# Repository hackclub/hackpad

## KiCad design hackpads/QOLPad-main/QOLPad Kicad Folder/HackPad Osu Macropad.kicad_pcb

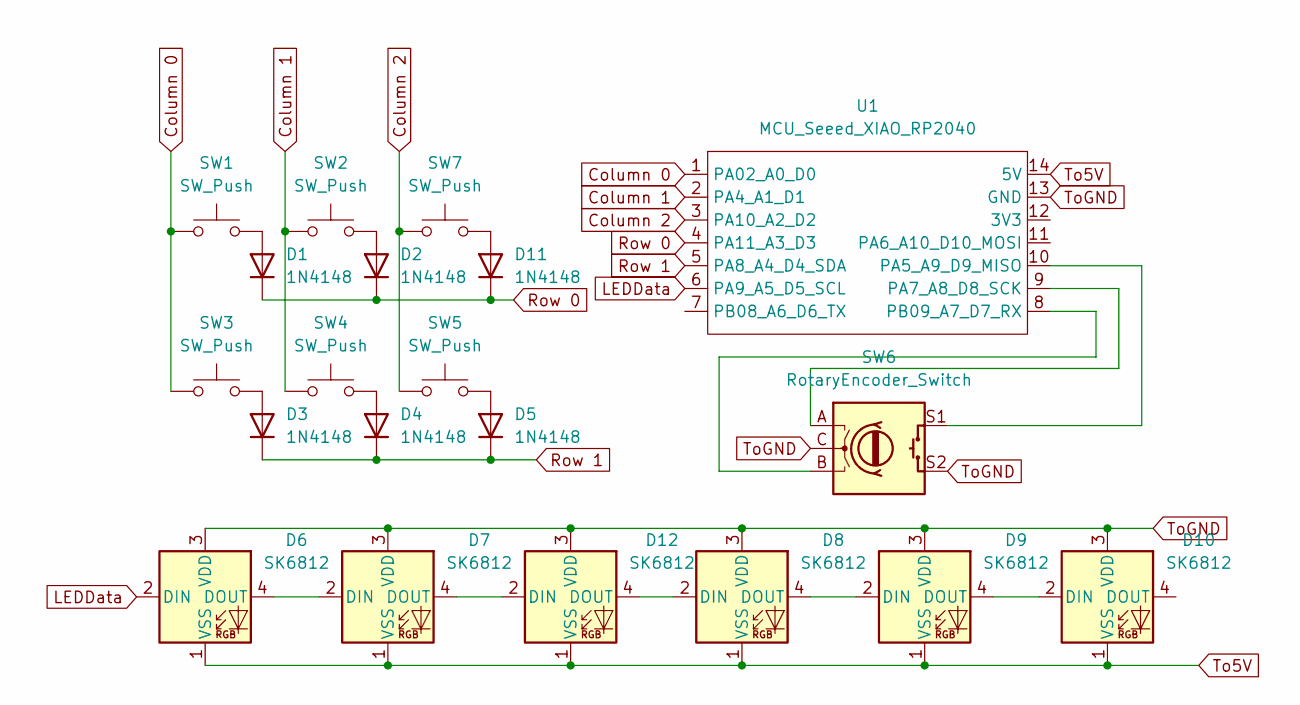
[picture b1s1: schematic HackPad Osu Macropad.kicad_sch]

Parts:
D1, D2, D3, D4, D5, D11: 1N4148; D_DO-35_SOD27_P7.62mm_Horizontal
D6, D7, D8, D9, D10, D12: SK6812; SK6812MINI-E
SW1, SW2, SW3, SW4, SW5, SW7: SW_Push; SW_Cherry_MX_1.00u_PCB
SW6: RotaryEncoder_Switch; RotaryEncoder_Alps_EC11E-Switch_Vertical_H20mm_CircularMoun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
U1: MCU_Seeed_XIAO_RP2040; XIAO-RP2040

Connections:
Column 0: SW1.1, SW3.1, U1.1 (PA02_A0_D0)
Column 1: SW2.1, SW4.1, U1.2 (PA4_A1_D1)
Column 2: SW5.1, SW7.1, U1.3 (PA10_A2_D2)
LEDData: D6.2 (DIN), U1.6 (PA9_A5_D5_SCL)
unnamed: D1.2 (A), SW1.2
unnamed: D2.2 (A), SW2.2
unnamed: D3.2 (A), SW3.2
unnamed: D4.2 (A), SW4.2
unnamed: D5.2 (A), SW5.2
unnamed: D6.4 (DOUT), D7.2 (DIN)
unnamed: D8.4 (DOUT), D9.2 (DIN)
unnamed: D9.4 (DOUT), D10.2 (DIN)
unnamed: D11.2 (A), SW7.2
unnamed: D7.4 (DOUT), D12.2 (DIN)
unnamed: D8.2 (DIN), D12.4 (DOUT)
unnamed: SW6.S1, U1.10 (PA5_A9_D9_MISO)
unnamed: SW6.A, U1.9 (PA7_A8_D8_SCK)
unnamed: SW6.B, U1.8 (PB09_A7_D7_RX)
Row 0: D1.1 (K), D2.1 (K), D11.1 (K), U1.4 (PA11_A3_D3)
Row 1: D3.1 (K), D4.1 (K), D5.1 (K), U1.5 (PA8_A4_D4_SDA)
To5V: D6.1 (VSS), D7.1 (VSS), D8.1 (VSS), D9.1 (VSS), D10.1 (VSS), D12.1 (VSS), U1.14 (5V)
ToGND: D6.3 (VDD), D7.3 (VDD), D8.3 (VDD), D9.3 (VDD), D10.3 (VDD), D12.3 (VDD), SW6.C, SW6.S2, U1.13 (GND)

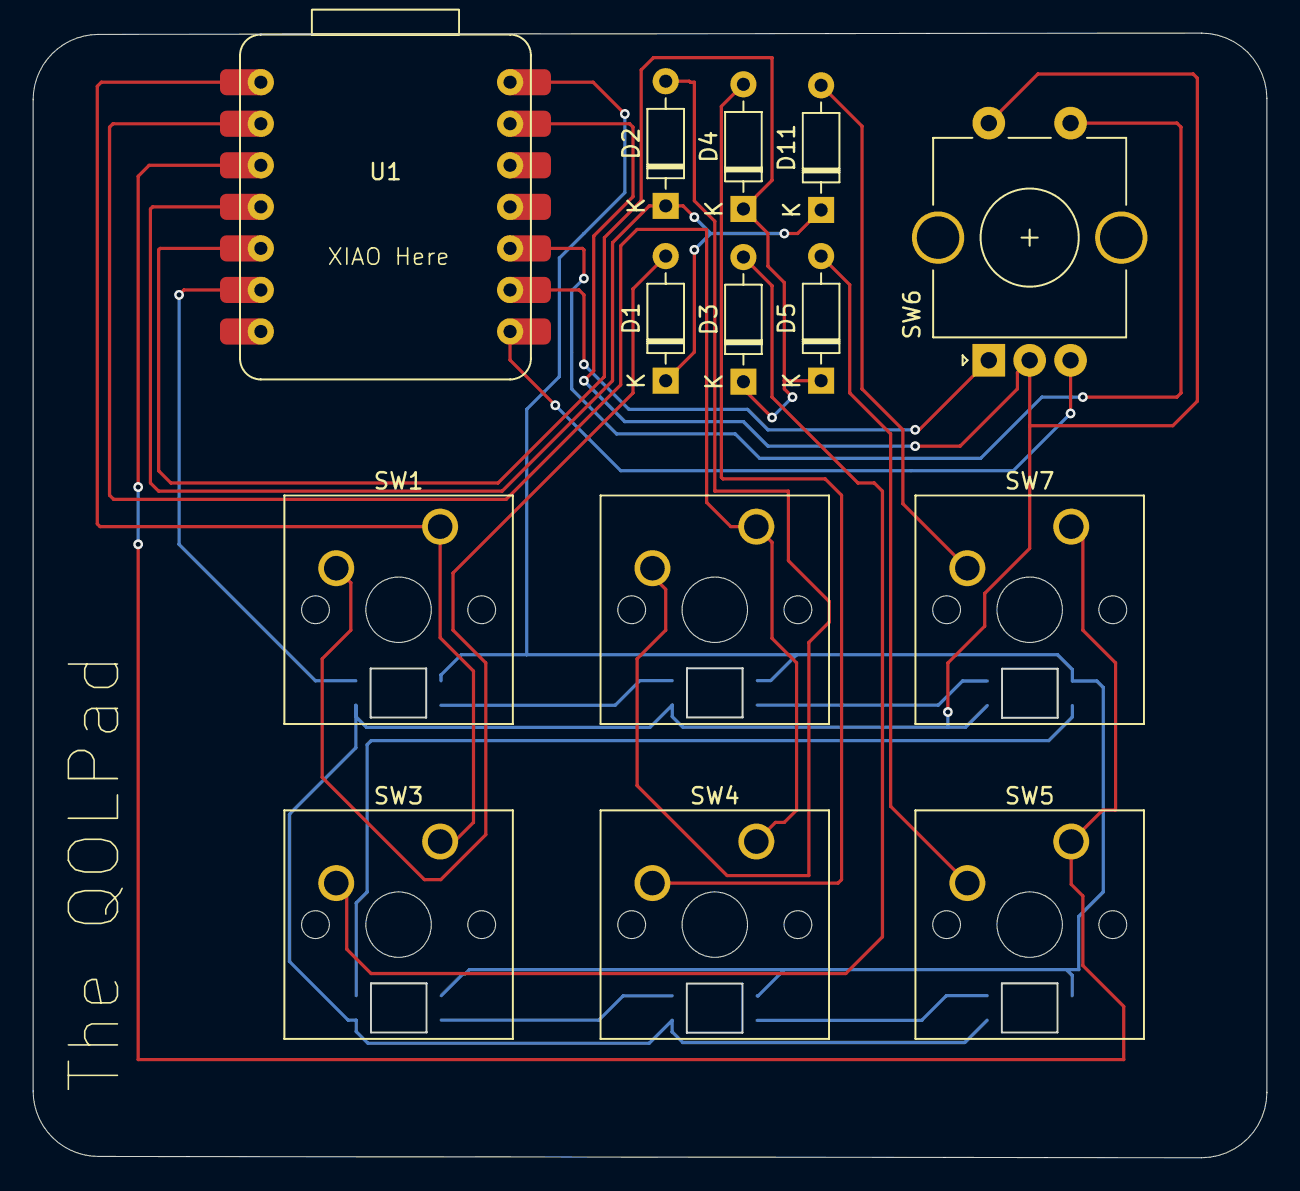
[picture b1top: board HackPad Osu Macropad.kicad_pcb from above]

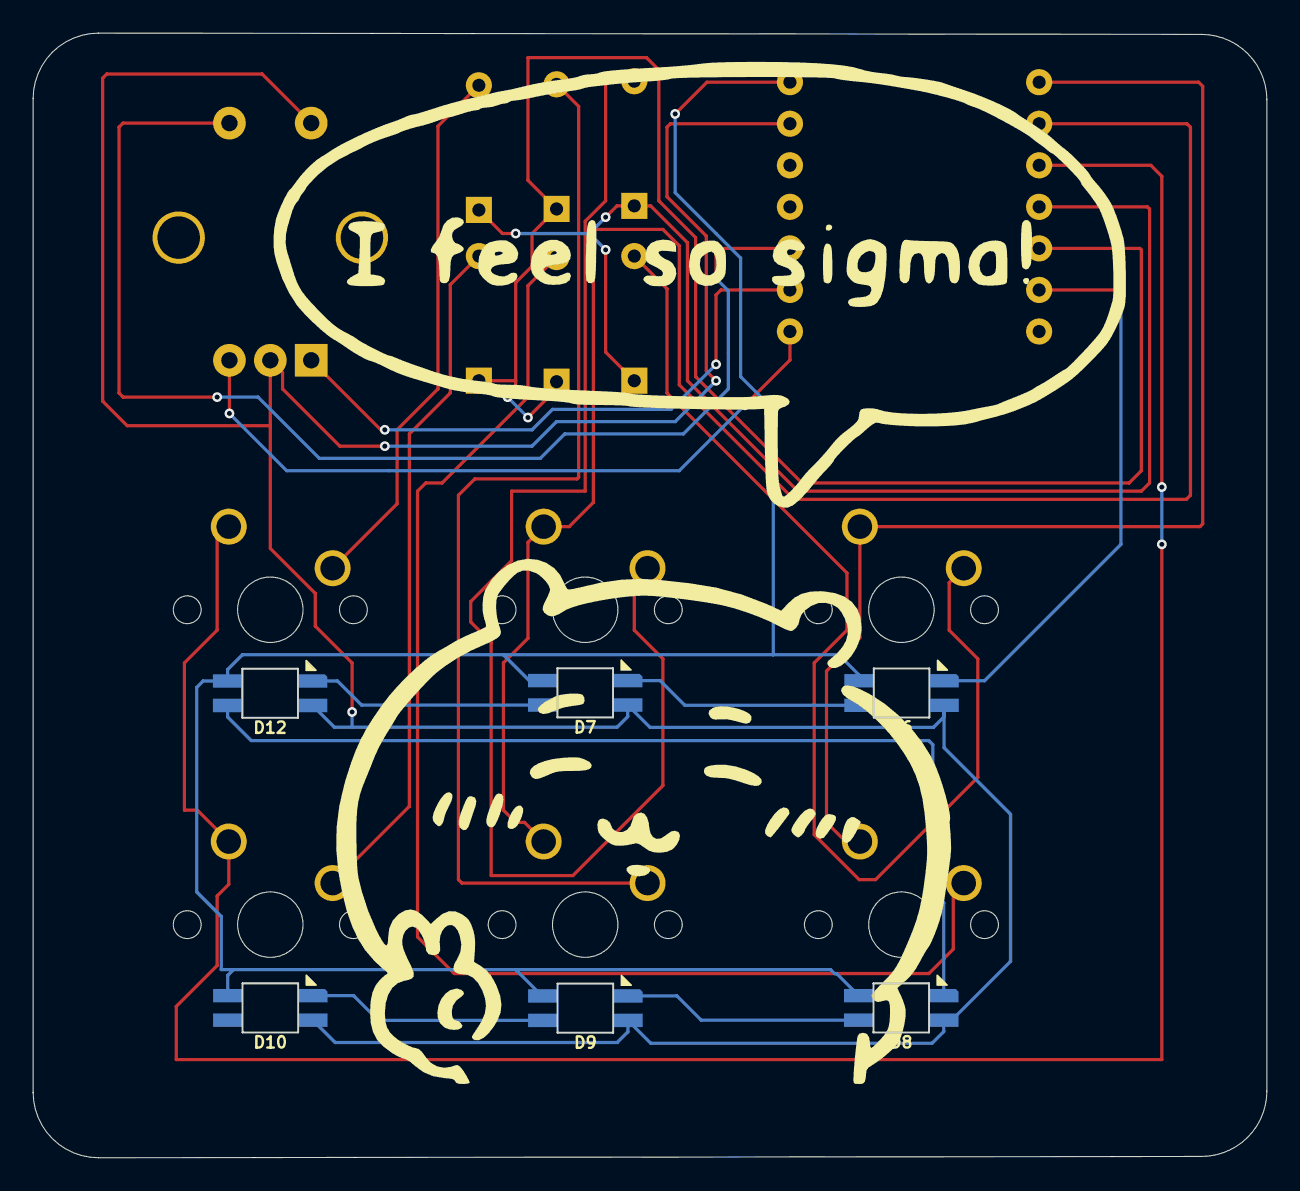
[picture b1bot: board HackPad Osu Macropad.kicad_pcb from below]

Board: 2 copper layers, 75.4 x 68.8 mm, 20 parts (6 on the bottom side), 22 nets.

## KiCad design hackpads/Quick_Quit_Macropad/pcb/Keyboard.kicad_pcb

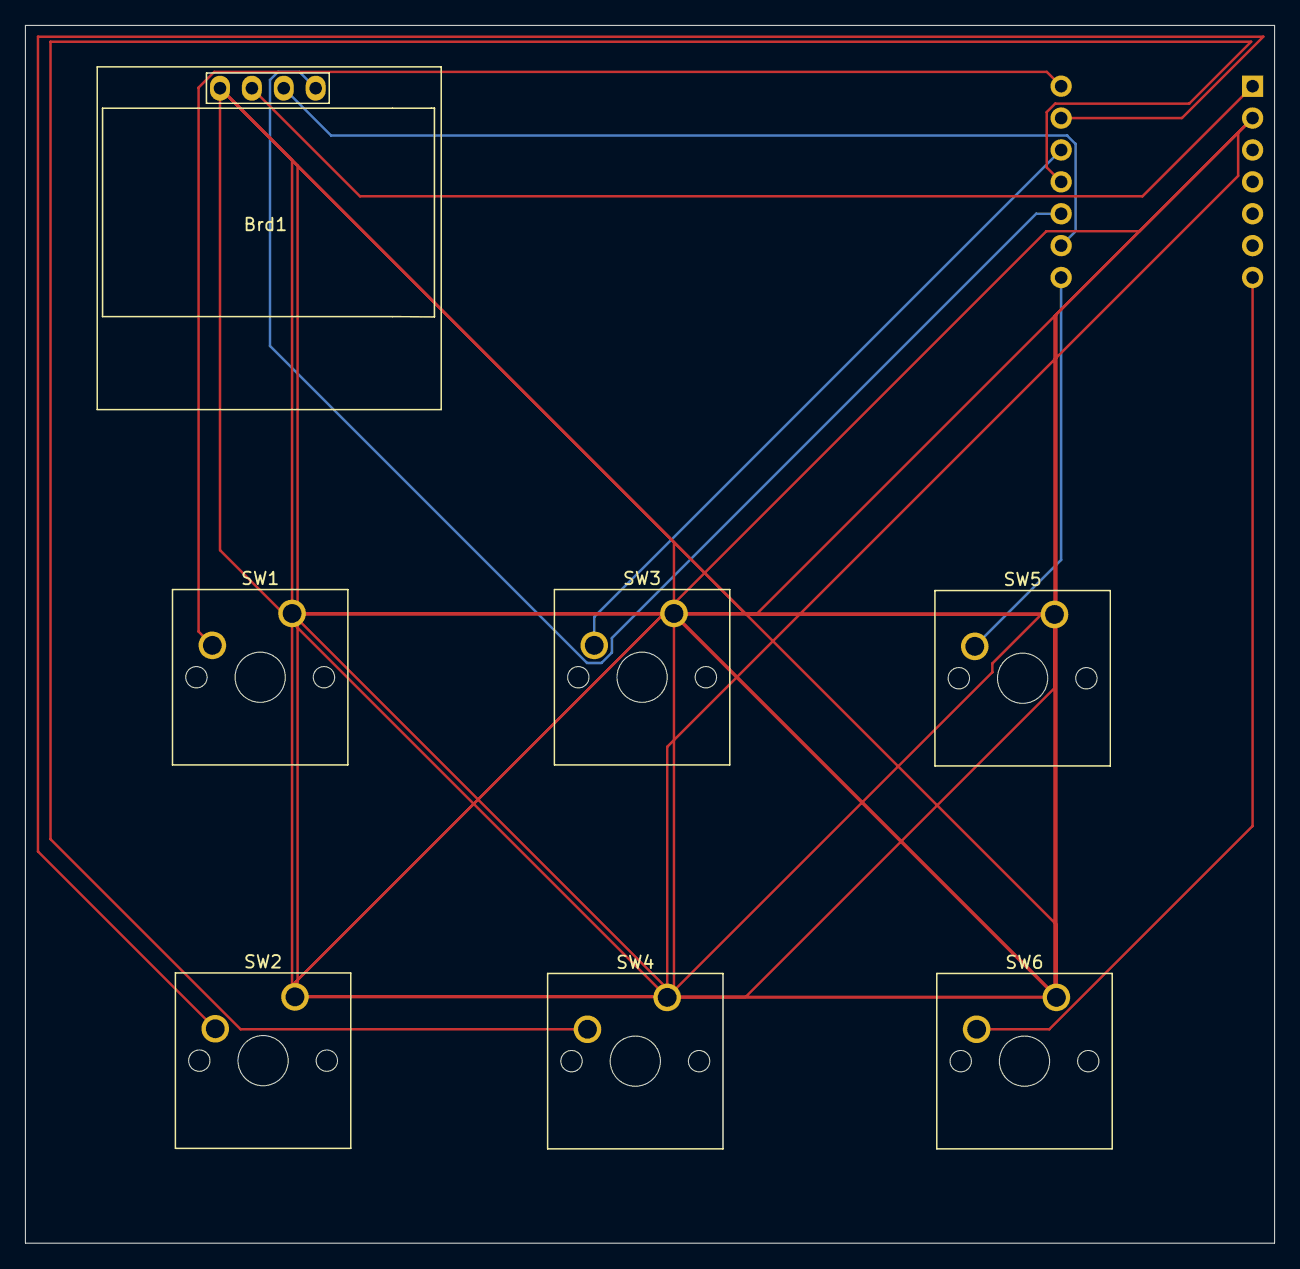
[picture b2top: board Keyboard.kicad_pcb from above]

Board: 2 copper layers, 99.5 x 97.0 mm, 8 parts (1 on the bottom side), 10 nets.

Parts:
Brd1: SSD1306; 128x64OLED
SW1, SW2, SW3, SW4, SW5, SW6: SW_Push; SW_Cherry_MX_1.00u_PCB
U1: Seeed Studio XIAO SAMD21; XIAO-Generic-Thruhole-14P-2.54-21X17.8MM

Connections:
1: SW1.2, U1.14 (5V)
2: SW2.2, U1.13 (GND)
3: SW3.2, U1.12 (3V3)
4: SW4.2, U1.11 (PA6_A10_D10_MOSI)
5: SW5.2, U1.8 (PB09_A7_D7_RX)
6: SW6.2, U1.7 (PB08_A6_D6_TX)
GND: Brd1.1 (GND), SW1.1, SW2.1, SW3.1, SW4.1, SW5.1, SW6.1, U1.2 (PA4_A1_D1)
SCL: Brd1.3 (SCL), U1.9 (PA7_A8_D8_SCK)
SDA: Brd1.4 (SDA), U1.10 (PA5_A9_D9_MISO)
VCC: Brd1.2 (VCC), U1.1 (PA02_A0_D0)

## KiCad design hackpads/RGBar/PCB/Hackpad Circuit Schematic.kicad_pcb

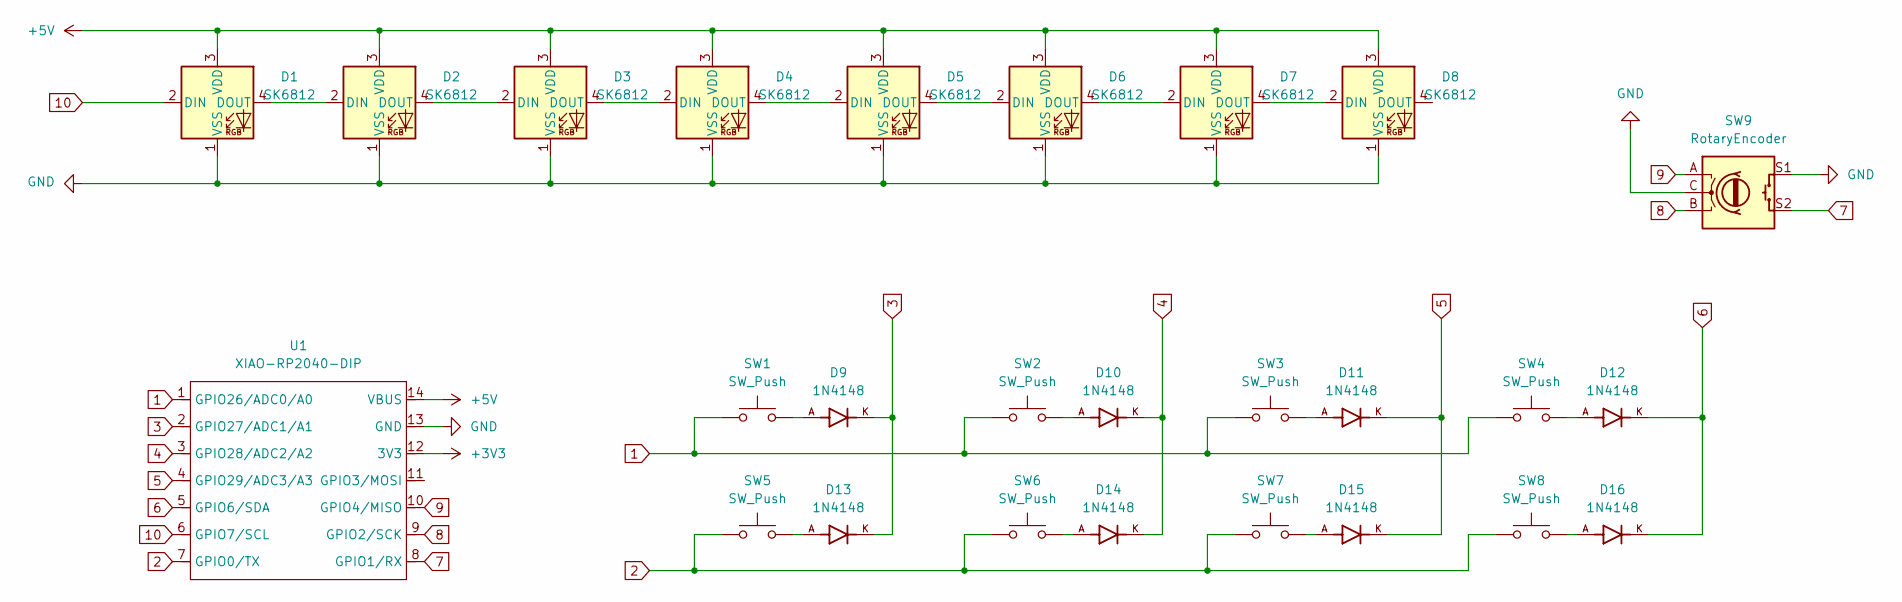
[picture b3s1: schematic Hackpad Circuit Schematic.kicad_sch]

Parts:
D1, D2, D3, D4, D5, D6, D7, D8: SK6812; MX-1U-SK6812Mini-E
D9, D10, D11, D12, D13, D14, D15, D16: 1N4148; DIOAD753W49L380D172B; PARTREV 5
SW1, SW2, SW3, SW4, SW5, SW6, SW7, SW8: SW_Push; SW_Cherry_MX_1.00u_PCB
SW9: RotaryEncoder; RotaryEncoder_Alps_EC11E-Switch_Vertical_H20mm_CircularMoun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
U1: XIAO-RP2040-DIP

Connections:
1: SW1.1, SW2.1, SW3.1, SW4.1, U1.1 (GPIO26/ADC0/A0)
2: SW5.1, SW6.1, SW7.1, SW8.1, U1.7 (GPIO0/TX)
3: D9.K, D13.K, U1.2 (GPIO27/ADC1/A1)
4: D10.K, D14.K, U1.3 (GPIO28/ADC2/A2)
5: D11.K, D15.K, U1.4 (GPIO29/ADC3/A3)
6: D12.K, D16.K, U1.5 (GPIO6/SDA)
7: SW9.S2, U1.8 (GPIO1/RX)
8: SW9.B, U1.9 (GPIO2/SCK)
9: SW9.A, U1.10 (GPIO4/MISO)
10: D1.2 (DIN), U1.6 (GPIO7/SCL)
+3V3: U1.12 (3V3)
+5V: D1.3 (VDD), D2.3 (VDD), D3.3 (VDD), D4.3 (VDD), D5.3 (VDD), D6.3 (VDD), D7.3 (VDD), D8.3 (VDD), U1.14 (VBUS)
GND: D1.1 (VSS), D2.1 (VSS), D3.1 (VSS), D4.1 (VSS), D5.1 (VSS), D6.1 (VSS), D7.1 (VSS), D8.1 (VSS), SW9.C, SW9.S1, U1.13 (GND)
unnamed: D1.4 (DOUT), D2.2 (DIN)
unnamed: D2.4 (DOUT), D3.2 (DIN)
unnamed: D3.4 (DOUT), D4.2 (DIN)
unnamed: D4.4 (DOUT), D5.2 (DIN)
unnamed: D5.4 (DOUT), D6.2 (DIN)
unnamed: D6.4 (DOUT), D7.2 (DIN)
unnamed: D7.4 (DOUT), D8.2 (DIN)
unnamed: D9.A, SW1.2
unnamed: D10.A, SW2.2
unnamed: D11.A, SW3.2
unnamed: D12.A, SW4.2
unnamed: D13.A, SW5.2
unnamed: D14.A, SW6.2
unnamed: D15.A, SW7.2
unnamed: D16.A, SW8.2

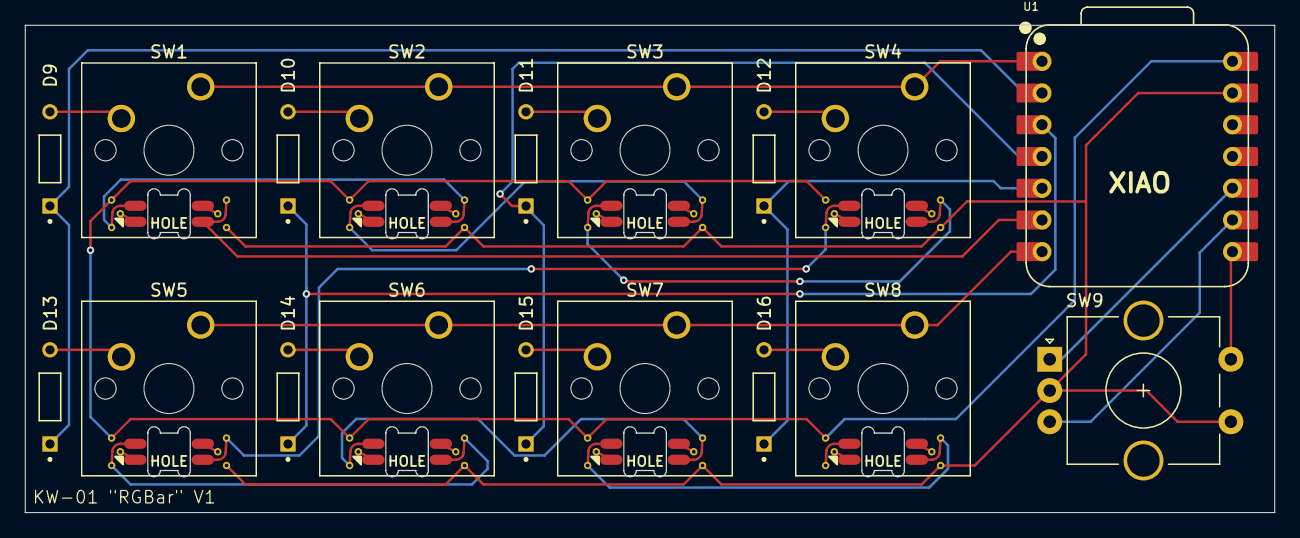
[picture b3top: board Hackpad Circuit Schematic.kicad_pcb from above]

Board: 2 copper layers, 100.0 x 39.0 mm, 26 parts (0 on the bottom side), 27 nets.

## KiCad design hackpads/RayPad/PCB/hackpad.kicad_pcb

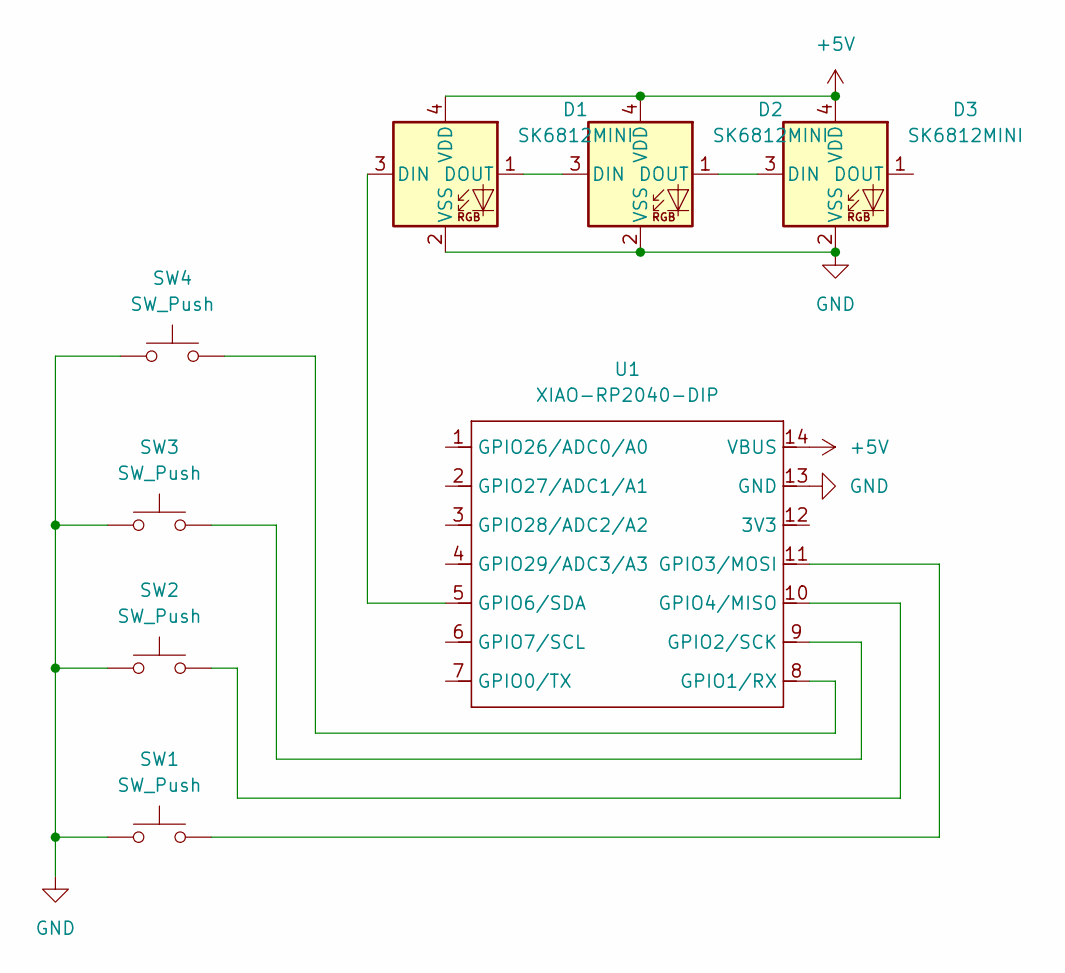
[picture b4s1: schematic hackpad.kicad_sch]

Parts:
D1, D2, D3: SK6812MINI; LED_SK6812MINI_PLCC4_3.5x3.5mm_P1.75mm
SW1, SW2, SW3, SW4: SW_Push; SW_Cherry_MX_1.00u_PCB
U1: XIAO-RP2040-DIP

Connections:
+5V: D1.4 (VDD), D2.4 (VDD), D3.4 (VDD), U1.14 (VBUS)
GND: D1.2 (VSS), D2.2 (VSS), D3.2 (VSS), SW1.1, SW2.1, SW3.1, SW4.1, U1.13 (GND)
unnamed: D1.3 (DIN), U1.5 (GPIO6/SDA)
unnamed: D1.1 (DOUT), D2.3 (DIN)
unnamed: D2.1 (DOUT), D3.3 (DIN)
unnamed: SW4.2, U1.8 (GPIO1/RX)
unnamed: SW3.2, U1.9 (GPIO2/SCK)
unnamed: SW1.2, U1.11 (GPIO3/MOSI)
unnamed: SW2.2, U1.10 (GPIO4/MISO)

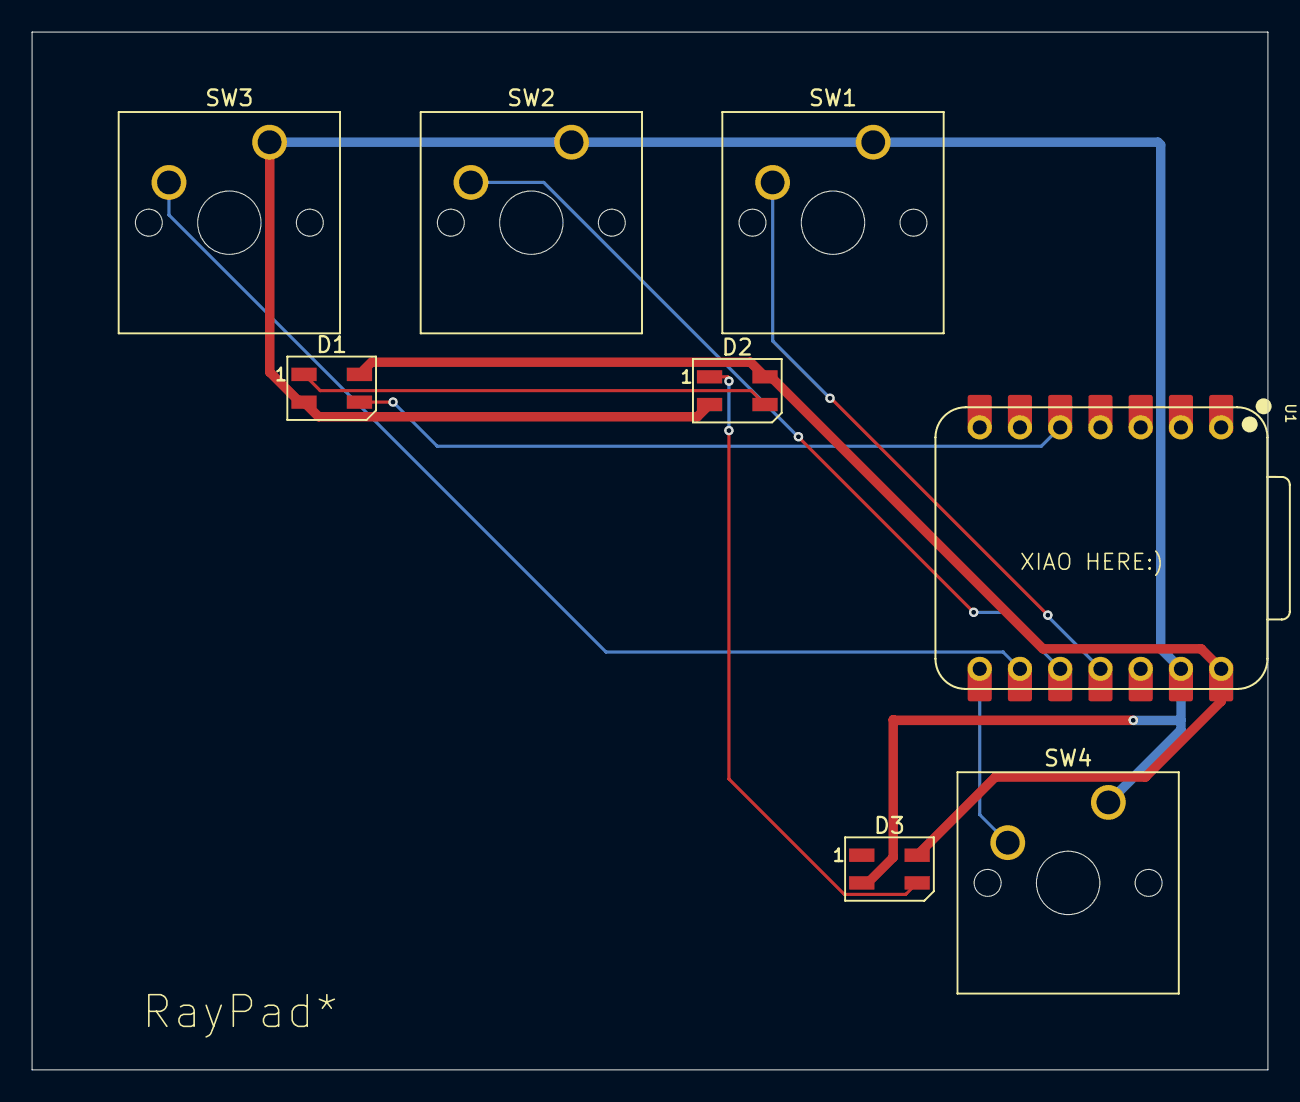
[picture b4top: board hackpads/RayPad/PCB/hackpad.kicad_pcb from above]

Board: 2 copper layers, 78.0 x 65.5 mm, 8 parts (0 on the bottom side), 9 nets.

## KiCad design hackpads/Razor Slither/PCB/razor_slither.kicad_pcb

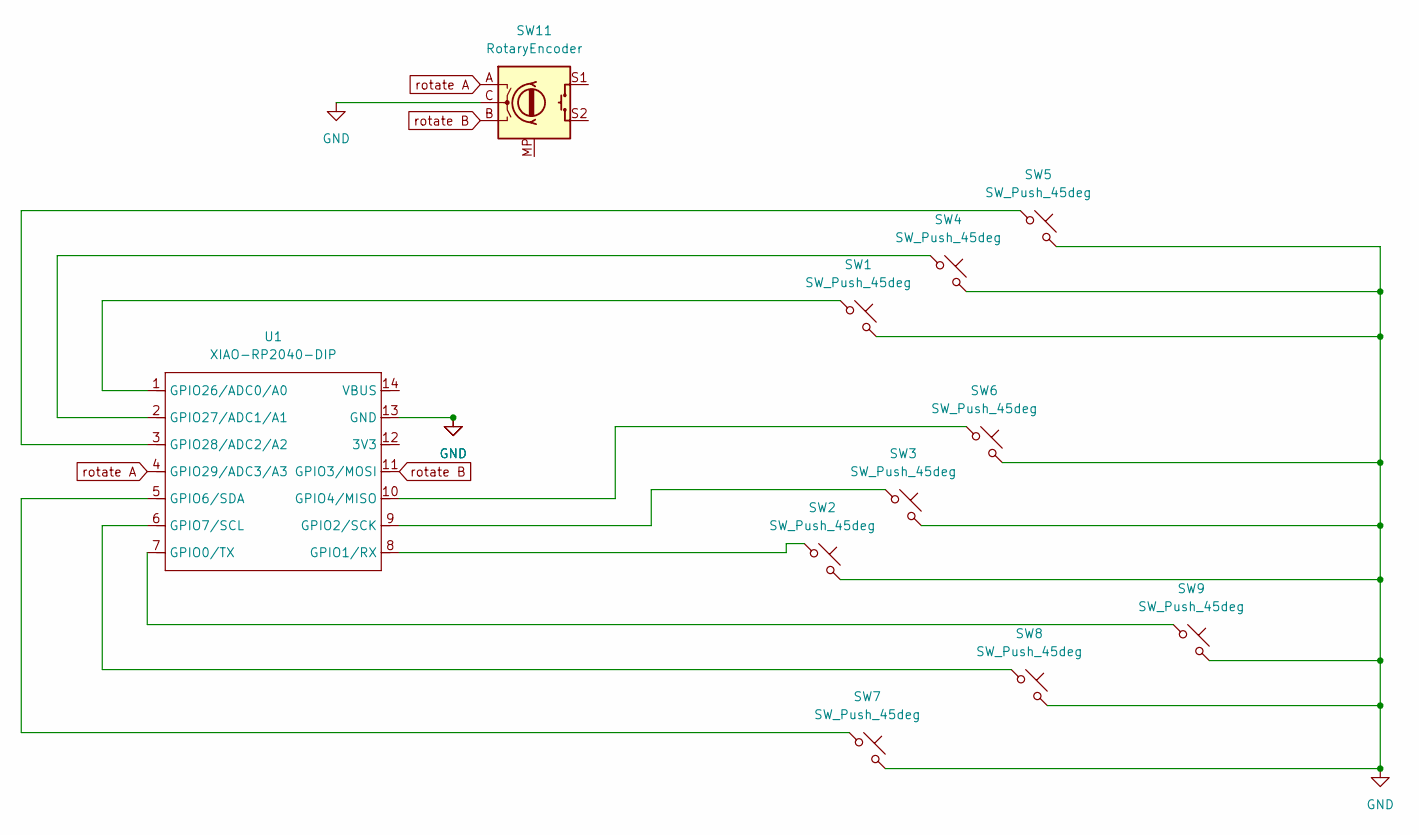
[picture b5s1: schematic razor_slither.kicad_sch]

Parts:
SW1, SW2, SW3, SW4, SW5, SW6, SW7, SW8, SW9: SW_Push_45deg; MX_PCB_1.00u
SW11: RotaryEncoder; RotaryEncoder_Alps_EC11E-Switch_Vertical_H20mm
U1: XIAO-RP2040-DIP

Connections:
GND: SW1.2, SW2.2, SW3.2, SW4.2, SW5.2, SW6.2, SW7.2, SW8.2, SW9.2, SW11.C, U1.13 (GND)
unnamed: SW9.1, U1.7 (GPIO0/TX)
unnamed: SW2.1, U1.8 (GPIO1/RX)
unnamed: SW3.1, U1.9 (GPIO2/SCK)
unnamed: SW6.1, U1.10 (GPIO4/MISO)
unnamed: SW7.1, U1.5 (GPIO6/SDA)
unnamed: SW8.1, U1.6 (GPIO7/SCL)
unnamed: SW1.1, U1.1 (GPIO26/ADC0/A0)
unnamed: SW4.1, U1.2 (GPIO27/ADC1/A1)
unnamed: SW5.1, U1.3 (GPIO28/ADC2/A2)
rotate A: SW11.A, U1.4 (GPIO29/ADC3/A3)
rotate B: SW11.B, U1.11 (GPIO3/MOSI)

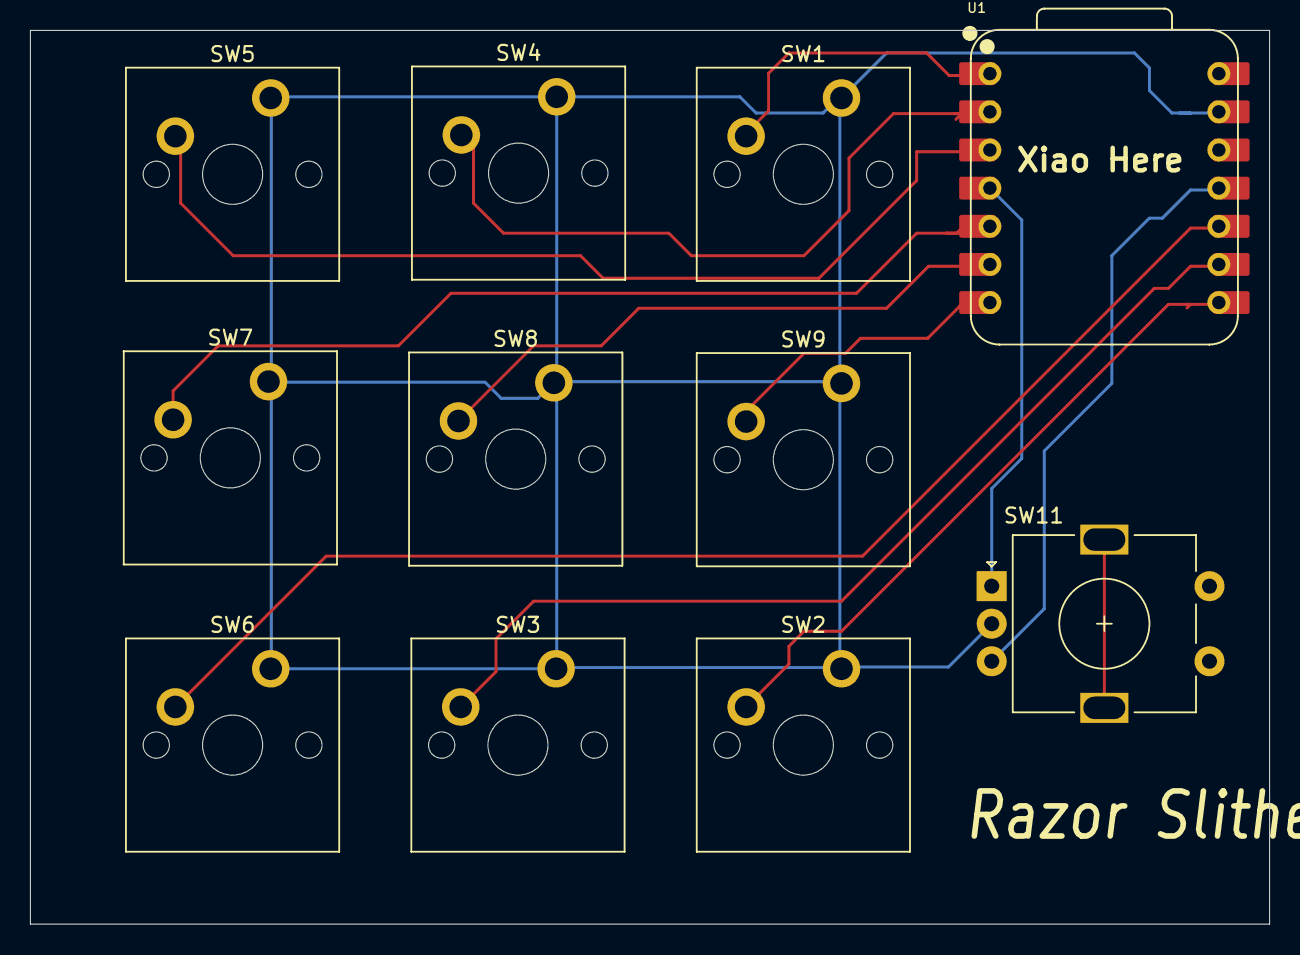
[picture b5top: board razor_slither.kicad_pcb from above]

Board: 2 copper layers, 82.5 x 59.5 mm, 11 parts (0 on the bottom side), 12 nets.

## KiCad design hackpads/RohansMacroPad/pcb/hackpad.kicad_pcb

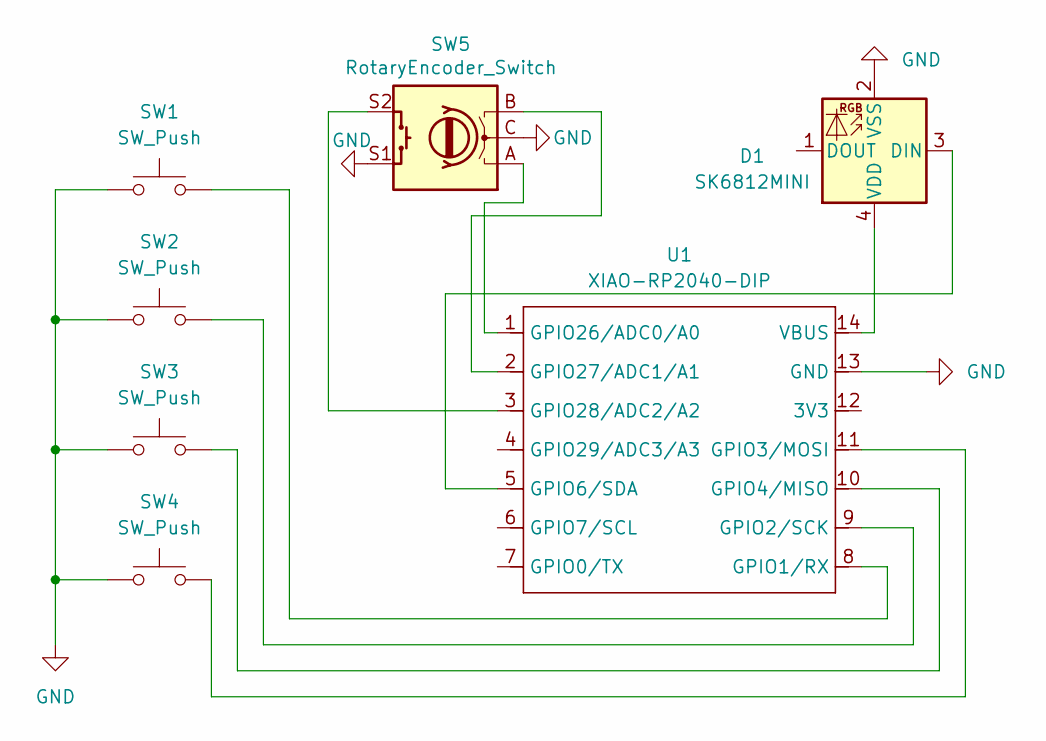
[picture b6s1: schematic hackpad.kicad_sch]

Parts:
D1: SK6812MINI; LED_SK6812MINI_PLCC4_3.5x3.5mm_P1.75mm
SW1, SW2, SW3, SW4: SW_Push; MX-Solderable-1U
SW5: RotaryEncoder_Switch; RotaryEncoder_Alps_EC11E-Switch_Vertical_H20mm
U1: XIAO-RP2040-DIP

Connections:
GND: D1.2 (VSS), SW1.1, SW2.1, SW3.1, SW4.1, SW5.C, SW5.S1, U1.13 (GND)
unnamed: D1.3 (DIN), U1.5 (GPIO6/SDA)
unnamed: D1.4 (VDD), U1.14 (VBUS)
unnamed: SW1.2, U1.8 (GPIO1/RX)
unnamed: SW2.2, U1.9 (GPIO2/SCK)
unnamed: SW4.2, U1.11 (GPIO3/MOSI)
unnamed: SW3.2, U1.10 (GPIO4/MISO)
unnamed: SW5.A, U1.1 (GPIO26/ADC0/A0)
unnamed: SW5.B, U1.2 (GPIO27/ADC1/A1)
unnamed: SW5.S2, U1.3 (GPIO28/ADC2/A2)

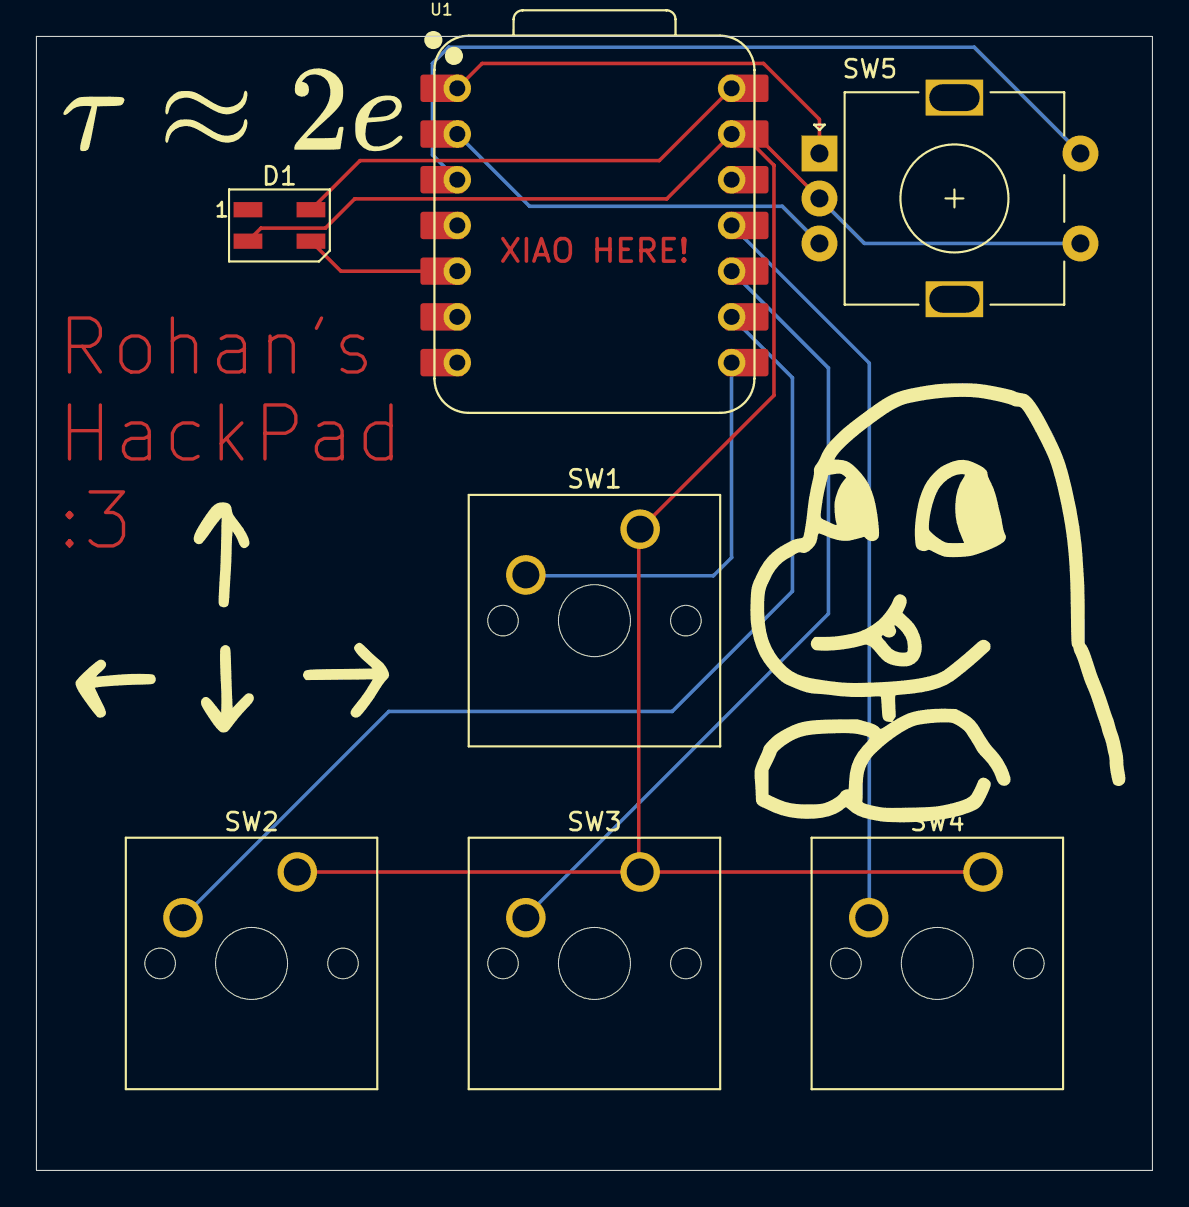
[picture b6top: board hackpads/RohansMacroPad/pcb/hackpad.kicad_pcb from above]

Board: 2 copper layers, 62.0 x 63.0 mm, 7 parts (0 on the bottom side), 10 nets.

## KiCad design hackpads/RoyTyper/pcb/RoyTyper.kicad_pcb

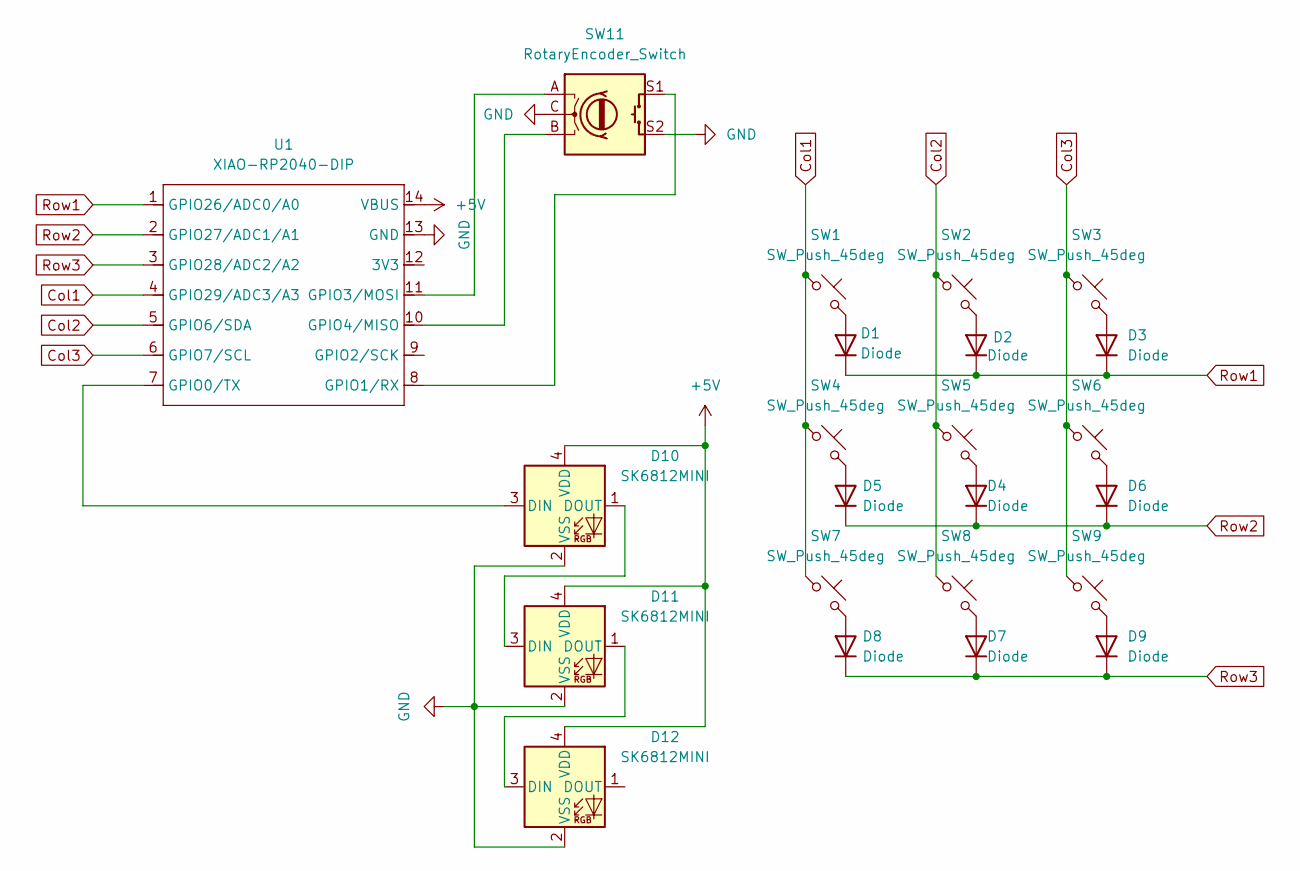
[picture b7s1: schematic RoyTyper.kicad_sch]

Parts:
D1, D2, D3, D4, D5, D6, D7, D8, D9: Diode; Diode_DO-35
D10, D11, D12: SK6812MINI; LED_SK6812MINI_PLCC4_3.5x3.5mm_P1.75mm
SW1, SW2, SW3, SW4, SW5, SW6, SW7, SW8, SW9: SW_Push_45deg; SW_Cherry_MX_1.00u_PCB
SW11: RotaryEncoder_Switch; RotaryEncoder_Alps_EC11E-Switch_Vertical_H20mm_CircularMoun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
U1: XIAO-RP2040-DIP

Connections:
+5V: D10.4 (VDD), D11.4 (VDD), D12.4 (VDD), U1.14 (VBUS)
Col1: SW1.1, SW4.1, SW7.1, U1.4 (GPIO29/ADC3/A3)
Col2: SW2.1, SW5.1, SW8.1, U1.5 (GPIO6/SDA)
Col3: SW3.1, SW6.1, SW9.1, U1.6 (GPIO7/SCL)
GND: D10.2 (VSS), D11.2 (VSS), D12.2 (VSS), SW11.C, SW11.S2, U1.13 (GND)
unnamed: D1.2 (A), SW1.2
unnamed: D2.2 (A), SW2.2
unnamed: D3.2 (A), SW3.2
unnamed: D4.2 (A), SW4.2
unnamed: D5.2 (A), SW5.2
unnamed: D6.2 (A), SW6.2
unnamed: D7.2 (A), SW7.2
unnamed: D8.2 (A), SW8.2
unnamed: D9.2 (A), SW9.2
unnamed: D10.3 (DIN), U1.7 (GPIO0/TX)
unnamed: D10.1 (DOUT), D11.3 (DIN)
unnamed: D11.1 (DOUT), D12.3 (DIN)
unnamed: SW11.S1, U1.8 (GPIO1/RX)
unnamed: SW11.A, U1.11 (GPIO3/MOSI)
unnamed: SW11.B, U1.10 (GPIO4/MISO)
Row1: D1.1 (K), D2.1 (K), D3.1 (K), U1.1 (GPIO26/ADC0/A0)
Row2: D4.1 (K), D5.1 (K), D6.1 (K), U1.2 (GPIO27/ADC1/A1)
Row3: D7.1 (K), D8.1 (K), D9.1 (K), U1.3 (GPIO28/ADC2/A2)

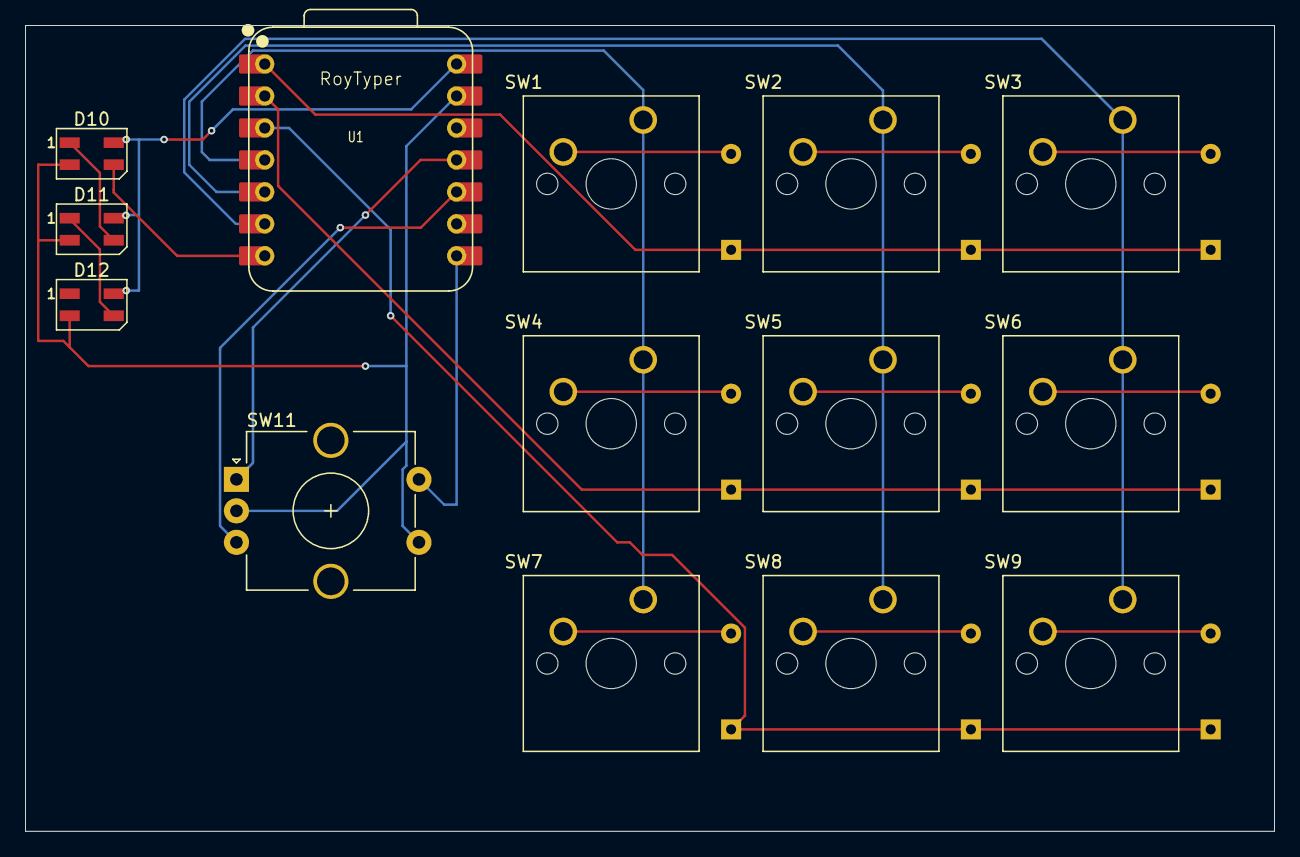
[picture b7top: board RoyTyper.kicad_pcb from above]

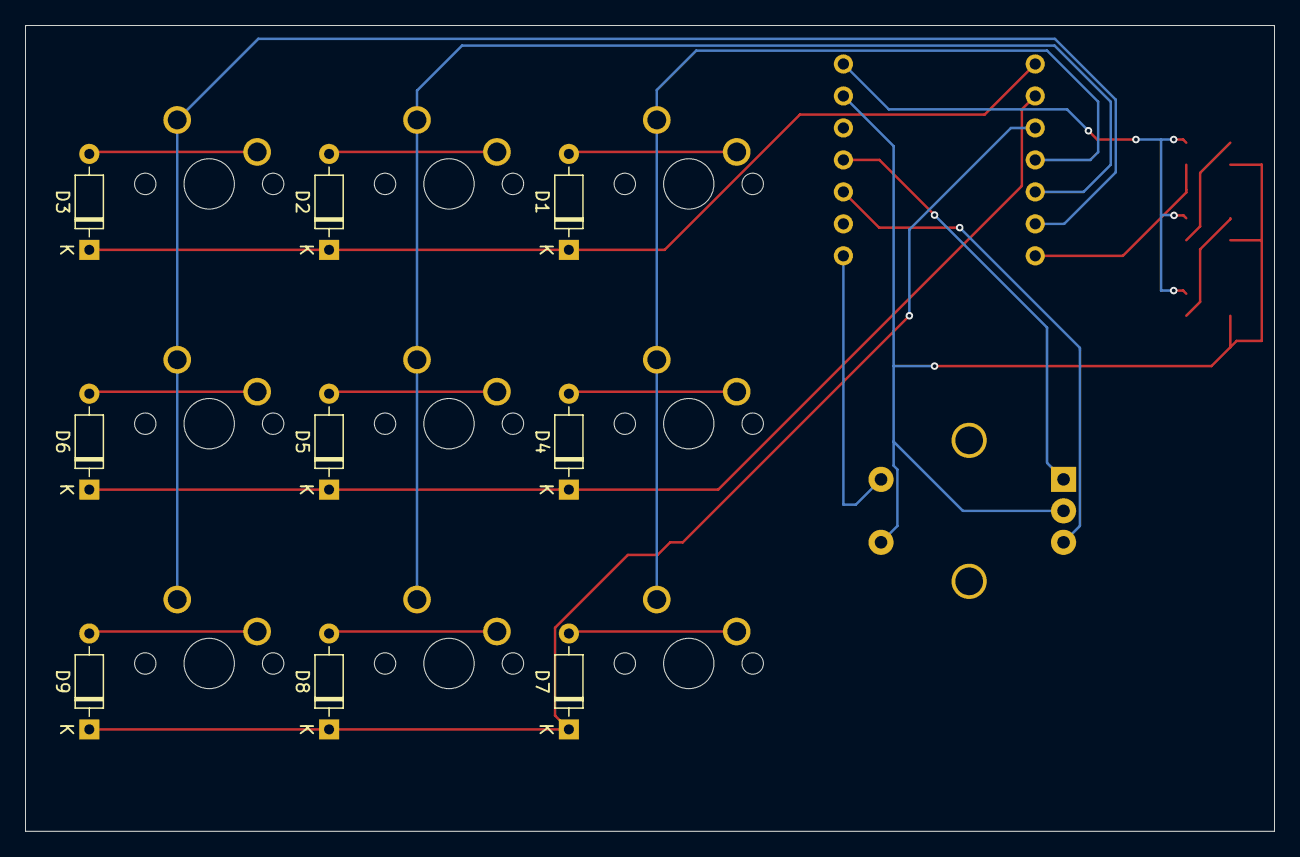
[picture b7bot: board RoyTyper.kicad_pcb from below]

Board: 2 copper layers, 99.2 x 64.0 mm, 23 parts (9 on the bottom side), 23 nets.
